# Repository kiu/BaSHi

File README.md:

# BaSHi
BaSHi - Bidirectional adapter for Sniffing Home appliances (isolated)

[Hajo](https://github.com/hn/) gave a [talk](https://media.ccc.de/v/39c3-hacking-washing-machines) on hacking home appliances at the [39C3](https://events.ccc.de/congress/2025/infos/startpage.html). That talk inspired me to build a simple, isolated, bidirectional D-Bus adapter to make tinkering with these devices easier.

# Warning
> [!WARNING]
> Household appliances work with high voltages and currents. Even if parts of the appliances operate at low voltages, they may or may not be isolated from earth and in case of a fault, can expose dangerous voltages. There is a good chance of death or serious injury. They might generate heat and steam, shake, vibrate, have rotating parts and get wet. Take appropriate safety measures.

| :zap: I'm neither responsible nor liable if you kill your cat, your spouse, yourself, or set your house on fire. You have been warned. BaSHi is intended to be used by experts, e.g., electricians.  |
|------------------------------------------|

# Usage
BaSHi can operate in two modes.

In <ins>non-isolated</ins> mode, the ESP32 is powered by the home appliance. Both jumpers must be shorted. This mode is intended for standalone operation. Do not connect the ESP32 USB port while BaSHi is connected to a home appliance.

In <ins>isolated</ins> mode, the ESP32 is electrically isolated from the home appliance. Bothe jumpers must be left open. This mode is intended for development. The ESP32 must be powered via its USB port.

Hint: Once you have identified the wires carrying D-BUS, use quick splice connectors (commonly used in automotive applications) to tap in BaSHi.

# Variants
BaSHi comes in two variants. Choose the variant based on the ESP32 board you want to use.

Note: While layout and pin usage differ between the two PCB variants, they share the same stencil, enclosure, and components (with the exception of J4 and J5).

## BaSHi-SM-1

Install: BaSHi-SM-1 is compatible with ESP32 boards of varying pin counts. The board must be bottom-aligned with the USB port at the lowest pin; the markings at the top provide additional guidance.

- [KiCad](BaSHi-SM-1/REV_A/kicad/): KiCad [schematic](BaSHi-SM-1/REV_A/BaSHi-SM-1-schematic.png), board and gerbers
- Compatibility: [ESP32 C3 Super Mini](https://www.espboards.dev/esp32/esp32-c3-super-mini/), [ESP32 C3 Super Mini Plus](https://www.espboards.dev/esp32/esp32-c3-super-mini-plus/), [ESP32 C6 Super Mini](https://www.espboards.dev/esp32/esp32-c6-super-mini/) and [ESP32 S3 Super Mini](https://www.espboards.dev/esp32/esp32-s3-super-mini/)

## BaSHi-ZERO-1

Install: For BaSHi-ZERO-1, all compatible ESP32 boards share the same pin count. Ensure the board is bottom-aligned with the USB port at the lowest pin.

- [KiCad](BaSHi-ZERO-1/REV_A/kicad/): KiCad [schematic](BaSHi-ZERO-1/REV_A/BaSHi-ZERO-1-schematic.png), board and gerbers
- Compatibility: [ESP32 C3 Zero](https://www.espboards.dev/esp32/esp32-c3-zero/), [ESP32 C6 Zero Mini](https://www.espboards.dev/esp32/esp32-c6-zero-mini/), [ESP32 S3 Zero](https://www.espboards.dev/esp32/esp32-s3-zero/)

## Common Files
The following files apply to both BaSHi variants.

- [Sketch](common/bsh-dbus-logger/): Adapted Arduino sketch (Bus2USB Bridge)
- [Mech](common/mech/): Simple OpenSCAD enclosure
- [BOM](common/BaSHi-boms.ods): Bills of materials ([PDF](common/BaSHi-boms.pdf))
- [Datasheets](common/datasheets/): Datasheets of main components

# Links
- https://github.com/hn/bsh-home-appliances/
- https://media.ccc.de/v/39c3-hacking-washing-machines
- https://de.wikipedia.org/wiki/RAST-Steckverbinder

# License
This project is licensed under the Creative Commons Attribution-NonCommercial 3.0 Unported (CC BY-NC 3.0) license.

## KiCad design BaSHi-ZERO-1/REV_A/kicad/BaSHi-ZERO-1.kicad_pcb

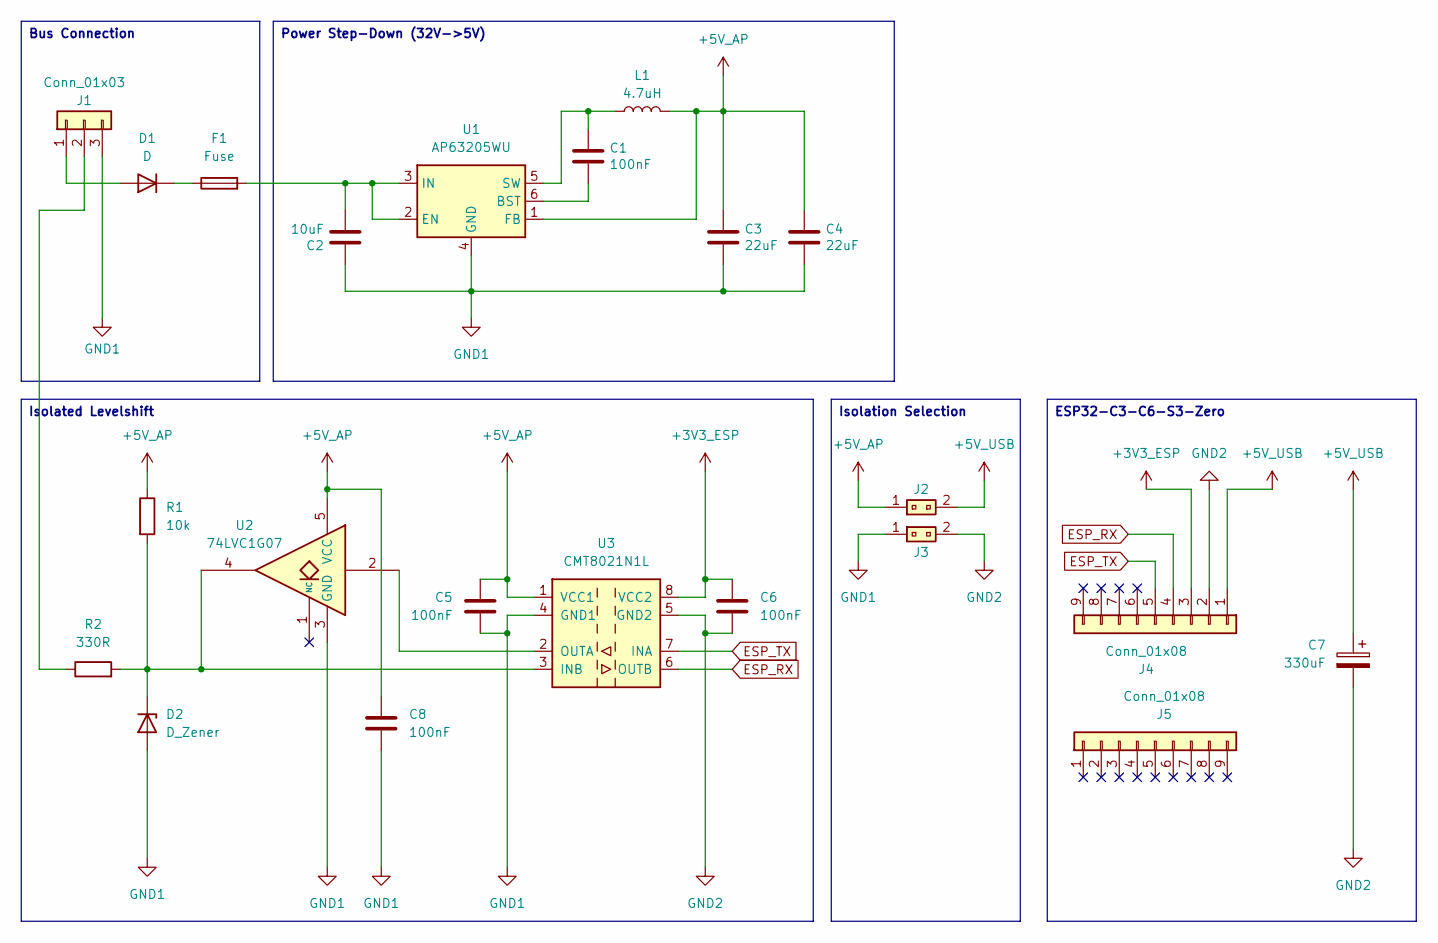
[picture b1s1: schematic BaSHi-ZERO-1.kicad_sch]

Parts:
C1, C5, C6, C8: 100nF; C_0805_2012Metric; LCSC C49678
C2: 10uF; C_1210_3225Metric; LCSC C576517
C3, C4: 22uF; C_0805_2012Metric; LCSC C6119895
C7: 330uF; CP_EIA-6032-28_Kemet-C; LCSC C11377
D1: D; D_SOD-123F; LCSC C3008061
D2: D_Zener; D_SOD-323; LCSC C110757
F1: Fuse; Fuse_0805_2012Metric; LCSC C25838740
J1: Conn_01x03; TerminalBlock_1x03_P5.08mm_Horizontal_WJ500V-5.08-03P-14-00A; LCSC C72334
J2, J3: 1x02_Jumper; PinHeader_1x03_1PMissing_P2.54mm_Vertical; LCSC C2937625
J4, J5: Conn_01x08; PinSocket_1x09_P2.54mm_Vertical; LCSC C27985234
L1: 4.7uH; L_SFE4018A-4R7M-F-HF_4x4x1.8mm; LCSC C5159668
R1: 10k; R_0805_2012Metric; LCSC C2930231
R2: 330R; R_0805_2012Metric; LCSC C2918550
U1: AP63205WU; TSOT-23-6; LCSC C2071056
U2: 74LVC1G07; SOT-23-5; LCSC C48391414
U3: CMT8021N1L; SOIC-8_3.9x4.9mm_P1.27mm; LCSC C32713171

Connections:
+3V3_ESP: C6.1, J4.3, U3.8 (VCC2)
+5V_AP: C3.1, C4.1, C5.2, C8.2, J2.1, L1.2, R1.1, U1.1 (FB), U2.5 (VCC), U3.1 (VCC1)
+5V_USB: C7.1, J2.2, J4.1
ESP_RX: J4.4, U3.6 (OUTB)
ESP_TX: J4.5, U3.7 (INA)
GND1: C2.1, C3.2, C4.2, C5.1, C8.1, D2.2 (A), J1.3, J3.1, U1.4 (GND), U2.3 (GND), U3.4 (GND1)
GND2: C6.2, C7.2, J3.2, J4.2, U3.5 (GND2)
unnamed: D1.2 (A), J1.1
unnamed: D1.1 (K), F1.1
unnamed: D2.1 (K), R1.2, R2.2, U2.4, U3.3 (INB)
unnamed: J1.2, R2.1
unnamed: C1.2, U1.6 (BST)
unnamed: C2.2, F1.2, U1.2 (EN), U1.3 (IN)
unnamed: C1.1, L1.1, U1.5 (SW)
unnamed: U2.2, U3.2 (OUTA)

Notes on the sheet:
Isolated Levelshift
Power Step-Down (32V->5V)
Bus Connection
Isolation Selection
ESP32-C3-C6-S3-Zero

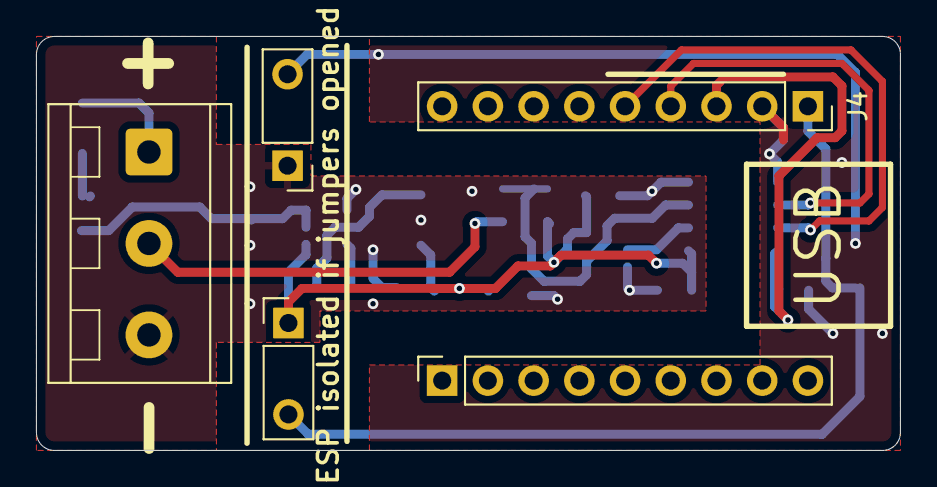
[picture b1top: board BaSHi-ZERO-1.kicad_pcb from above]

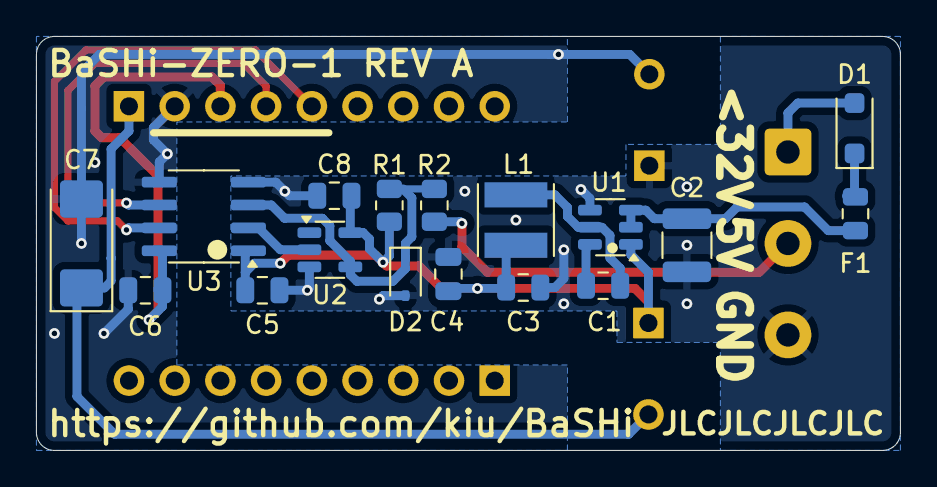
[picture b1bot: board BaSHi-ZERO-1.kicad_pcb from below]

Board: 2 copper layers, 48.0 x 23.0 mm, 22 parts (17 on the bottom side), 15 nets.

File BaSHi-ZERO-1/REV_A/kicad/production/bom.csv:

Designator,Footprint,Quantity,Value,LCSC Part #
"C1, C5, C6, C8",0805,4,100nF,C49678
C2,1210,1,10uF,C576517
"C3, C4",0805,2,22uF,C6119895
C7,CP_EIA-6032-28_Kemet-C,1,330uF,C11377
D1,D_SOD-123F,1,D,C3008061
D2,D_SOD-323,1,D_Zener,C110757
F1,0805,1,Fuse,C25838740
J1,TerminalBlock_1x03_P5.08mm_Horizontal_WJ500V-5.08-03P-14-00A,1,Conn_01x03,C72334
"J2, J3",PinHeader_1x03_1PMissing_P2.54mm_Vertical,2,1x02_Jumper,C2937625
"J4, J5",PinSocket_1x09_P2.54mm_Vertical,2,Conn_01x08,C27985234
L1,L_SFE4018A-4R7M-F-HF_4x4x1.8mm,1,4.7uH,C5159668
R1,0805,1,10k,C2930231
R2,0805,1,330R,C2918550
U1,TSOT-23-6,1,AP63205WU,C2071056
U2,SOT-23-5,1,74LVC1G07,C48391414
U3,SOIC-8_3.9x4.9mm_P1.27mm,1,CMT8021N1L,C32713171
